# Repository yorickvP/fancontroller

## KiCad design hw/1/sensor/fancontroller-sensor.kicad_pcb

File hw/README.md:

# Hardware revisions

## Rev 1 (10-2022)
Initial prototype production series, with several issues:
* L302 has an unusable footprint, replace with Farnell 2434098 2.5uH
* 12V is 2.5V
    * R305 -> LCSC code is for 1K
    * 16K & 1K8
* Temperature sensor is placed right next to ESP32
* Would like to toggle vfan rails individually

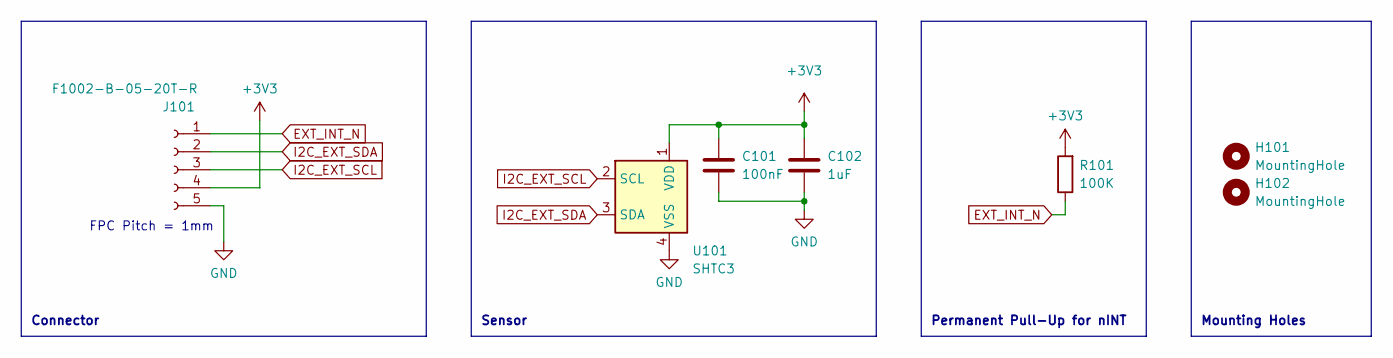
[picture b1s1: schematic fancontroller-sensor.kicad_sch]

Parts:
C101: 100nF; C_0402_1005Metric; LCSC C307331
C102: 1uF; C_0402_1005Metric; LCSC C52923
H101, H102: MountingHole; MountingHole_2.2mm_M2
J101: F1002-B-05-20T-R; LCSC C3015089
R101: 100K; R_0402_1005Metric; LCSC C25741
U101: SHTC3; Sensirion_DFN-4-1EP_2x2mm_P1mm_EP0.7x1.6mm

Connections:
+3V3: C101.1, C102.1, J101.4, R101.2, U101.1 (VDD)
EXT_INT_N: J101.1, R101.1
GND: C101.2, C102.2, J101.5, U101.4 (VSS)
I2C_EXT_SCL: J101.3, U101.2 (SCL)
I2C_EXT_SDA: J101.2, U101.3 (SDA)

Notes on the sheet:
Mounting Holes
Connector
Sensor
FPC Pitch = 1mm
Permanent Pull-Up for nINT

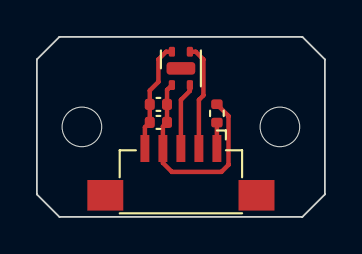
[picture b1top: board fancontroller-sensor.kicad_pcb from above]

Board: 2 copper layers, 16.0 x 10.0 mm, 7 parts (0 on the bottom side), 5 nets.

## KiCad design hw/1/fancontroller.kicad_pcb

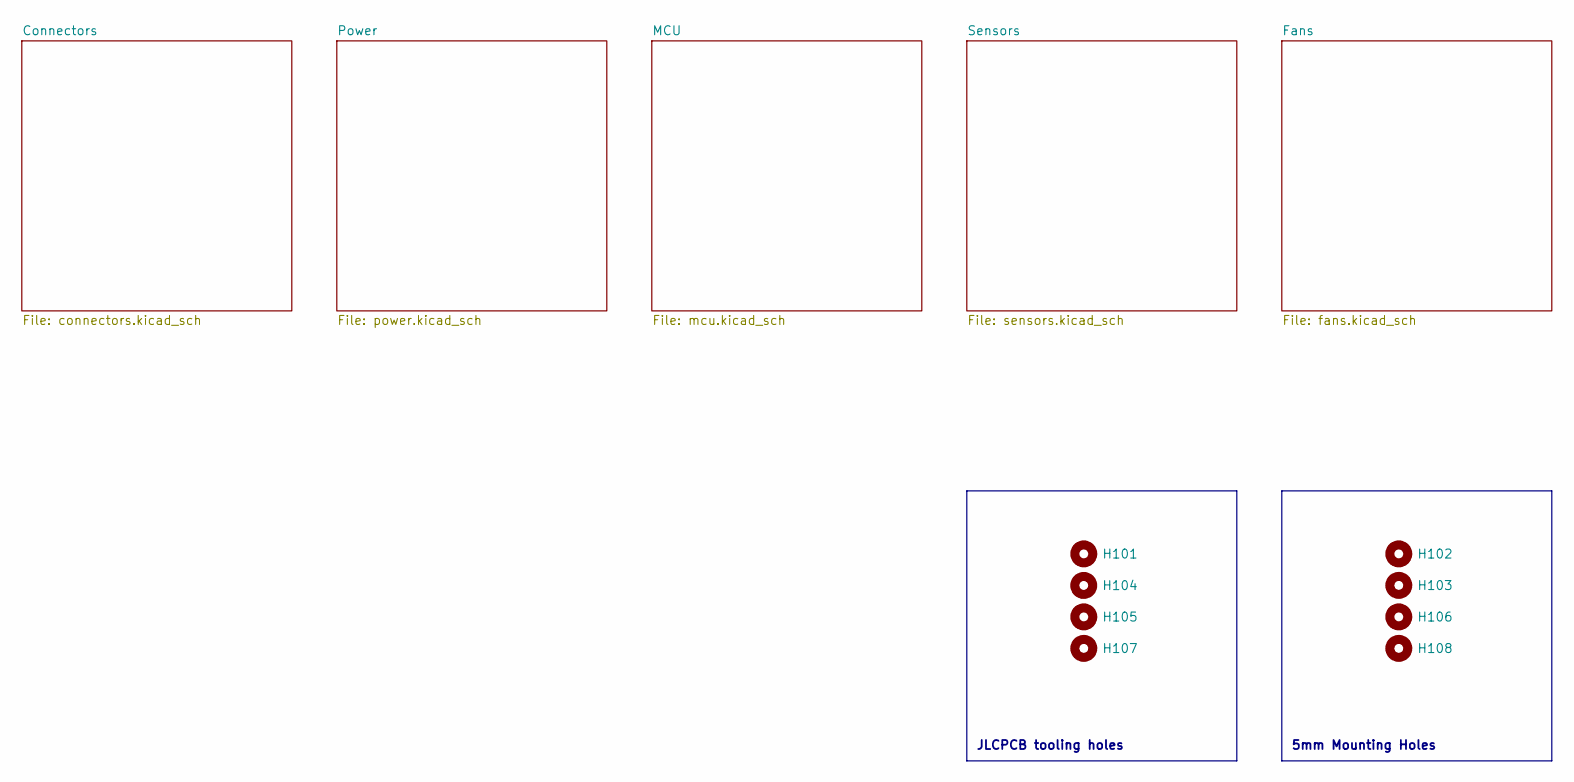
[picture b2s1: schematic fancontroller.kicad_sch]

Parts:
H101, H104, H105, H107: ToolingHole; JLCPCB tooling hole
H102, H103, H106, H108: MountingHole; MountingHole_5mm_Keepout

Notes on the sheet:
JLCPCB tooling holes
5mm Mounting Holes

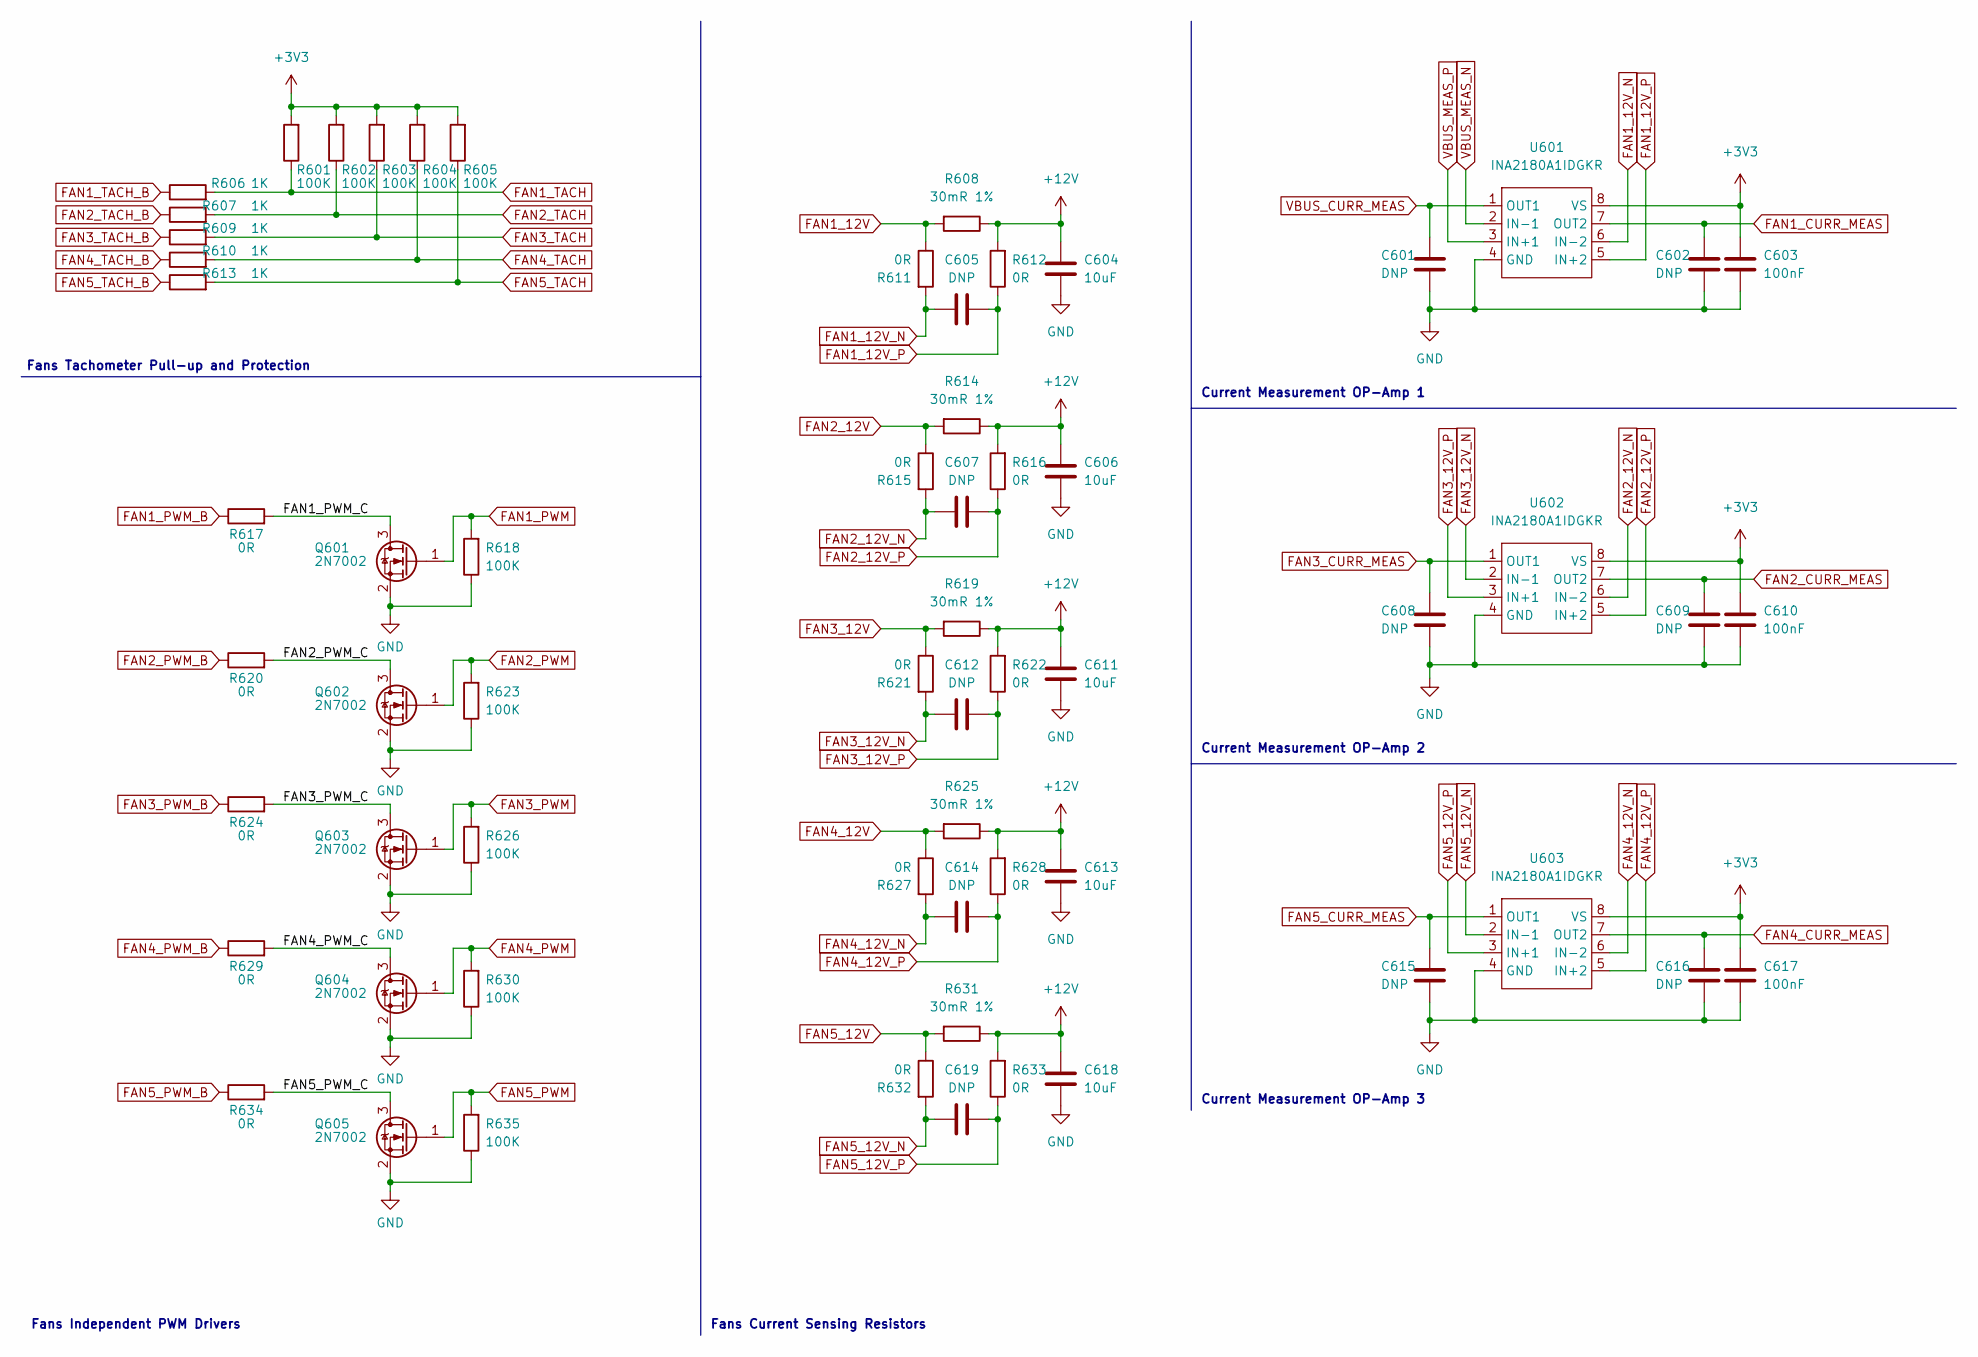
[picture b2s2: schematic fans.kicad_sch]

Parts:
C601, C602, C605, C607, C608, C609, C612, C614, C615, C616, C619: DNP; C_0402_1005Metric
C603, C610, C617: 100nF; C_0402_1005Metric; LCSC C307331
C604, C606, C611, C613, C618: 10uF; C_0805_2012Metric; LCSC C15850
Q601, Q602, Q603, Q604, Q605: 2N7002; SOT-23; LCSC C8545
R601, R602, R603, R604, R605, R618, R623, R626, R630, R635: 100K; R_0402_1005Metric; LCSC C25741
R606, R607, R609, R610, R613: 1K; R_0402_1005Metric; LCSC C11702
R608, R614, R619, R625, R631: 30mR 1%; R_0805_2012Metric; LCSC C247605
R611, R612, R615, R616, R617, R620, R621, R622, R624, R627, R628, R629, R632, R633, R634: 0R; R_0402_1005Metric; LCSC C17168
U601, U602, U603: INA2180A1IDGKR; VSSOP-8_3.0x3.0mm_P0.65mm; LCSC C2058454

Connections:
+3V3: C603.1, C610.1, C617.1, R601.2, R602.2, R603.2, R604.2, R605.2, U601.8 (VS), U602.8 (VS), U603.8 (VS); also elsewhere on the board
+12V: C604.1, C606.1, C611.1, C613.1, C618.1, R608.1, R612.2, R614.1, R616.2, R619.1, R622.2, R625.1, R628.2, R631.1, R633.2; also elsewhere on the board
/Fans/FAN1_PWM_C: Q601.3 (D), R617.2
/Fans/FAN2_PWM_C: Q602.3 (D), R620.2
/Fans/FAN3_PWM_C: Q603.3 (D), R624.2
/Fans/FAN4_PWM_C: Q604.3 (D), R629.2
/Fans/FAN5_PWM_C: Q605.3 (D), R634.2
FAN1_12V: R608.2, R611.1; also elsewhere on the board
FAN1_12V_N: C605.1, R611.2, U601.6 (IN-2)
FAN1_12V_P: C605.2, R612.1, U601.5 (IN+2)
FAN1_CURR_MEAS: C602.1, U601.7 (OUT2); also elsewhere on the board
FAN1_PWM: Q601.1 (G), R618.2; also elsewhere on the board
FAN1_PWM_B: R617.1; also elsewhere on the board
FAN1_TACH: R601.1, R606.2; also elsewhere on the board
FAN1_TACH_B: R606.1; also elsewhere on the board
FAN2_12V: R614.2, R615.1; also elsewhere on the board
FAN2_12V_N: C607.1, R615.2, U602.6 (IN-2)
FAN2_12V_P: C607.2, R616.1, U602.5 (IN+2)
FAN2_CURR_MEAS: C609.1, U602.7 (OUT2); also elsewhere on the board
FAN2_PWM: Q602.1 (G), R623.2; also elsewhere on the board
FAN2_PWM_B: R620.1; also elsewhere on the board
FAN2_TACH: R602.1, R607.2; also elsewhere on the board
FAN2_TACH_B: R607.1; also elsewhere on the board
FAN3_12V: R619.2, R621.1; also elsewhere on the board
FAN3_12V_N: C612.1, R621.2, U602.2 (IN-1)
FAN3_12V_P: C612.2, R622.1, U602.3 (IN+1)
FAN3_CURR_MEAS: C608.1, U602.1 (OUT1); also elsewhere on the board
FAN3_PWM: Q603.1 (G), R626.2; also elsewhere on the board
FAN3_PWM_B: R624.1; also elsewhere on the board
FAN3_TACH: R603.1, R609.2; also elsewhere on the board
FAN3_TACH_B: R609.1; also elsewhere on the board
FAN4_12V: R625.2, R627.1; also elsewhere on the board
FAN4_12V_N: C614.1, R627.2, U603.6 (IN-2)
FAN4_12V_P: C614.2, R628.1, U603.5 (IN+2)
FAN4_CURR_MEAS: C616.1, U603.7 (OUT2); also elsewhere on the board
FAN4_PWM: Q604.1 (G), R630.2; also elsewhere on the board
FAN4_PWM_B: R629.1; also elsewhere on the board
FAN4_TACH: R604.1, R610.2; also elsewhere on the board
FAN4_TACH_B: R610.1; also elsewhere on the board
FAN5_12V: R631.2, R632.1; also elsewhere on the board
FAN5_12V_N: C619.1, R632.2, U603.2 (IN-1)
FAN5_12V_P: C619.2, R633.1, U603.3 (IN+1)
FAN5_CURR_MEAS: C615.1, U603.1 (OUT1); also elsewhere on the board
FAN5_PWM: Q605.1 (G), R635.2; also elsewhere on the board
FAN5_PWM_B: R634.1; also elsewhere on the board
FAN5_TACH: R605.1, R613.2; also elsewhere on the board
FAN5_TACH_B: R613.1; also elsewhere on the board
VBUS_CURR_MEAS: C601.1, U601.1 (OUT1); also elsewhere on the board
VBUS_MEAS_N: U601.2 (IN-1); also elsewhere on the board
VBUS_MEAS_P: U601.3 (IN+1); also elsewhere on the board

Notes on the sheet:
Current Measurement OP-Amp 3
Fans Independent PWM Drivers
Current Measurement OP-Amp 1
Fans Current Sensing Resistors
Fans Tachometer Pull-up and Protection
Current Measurement OP-Amp 2

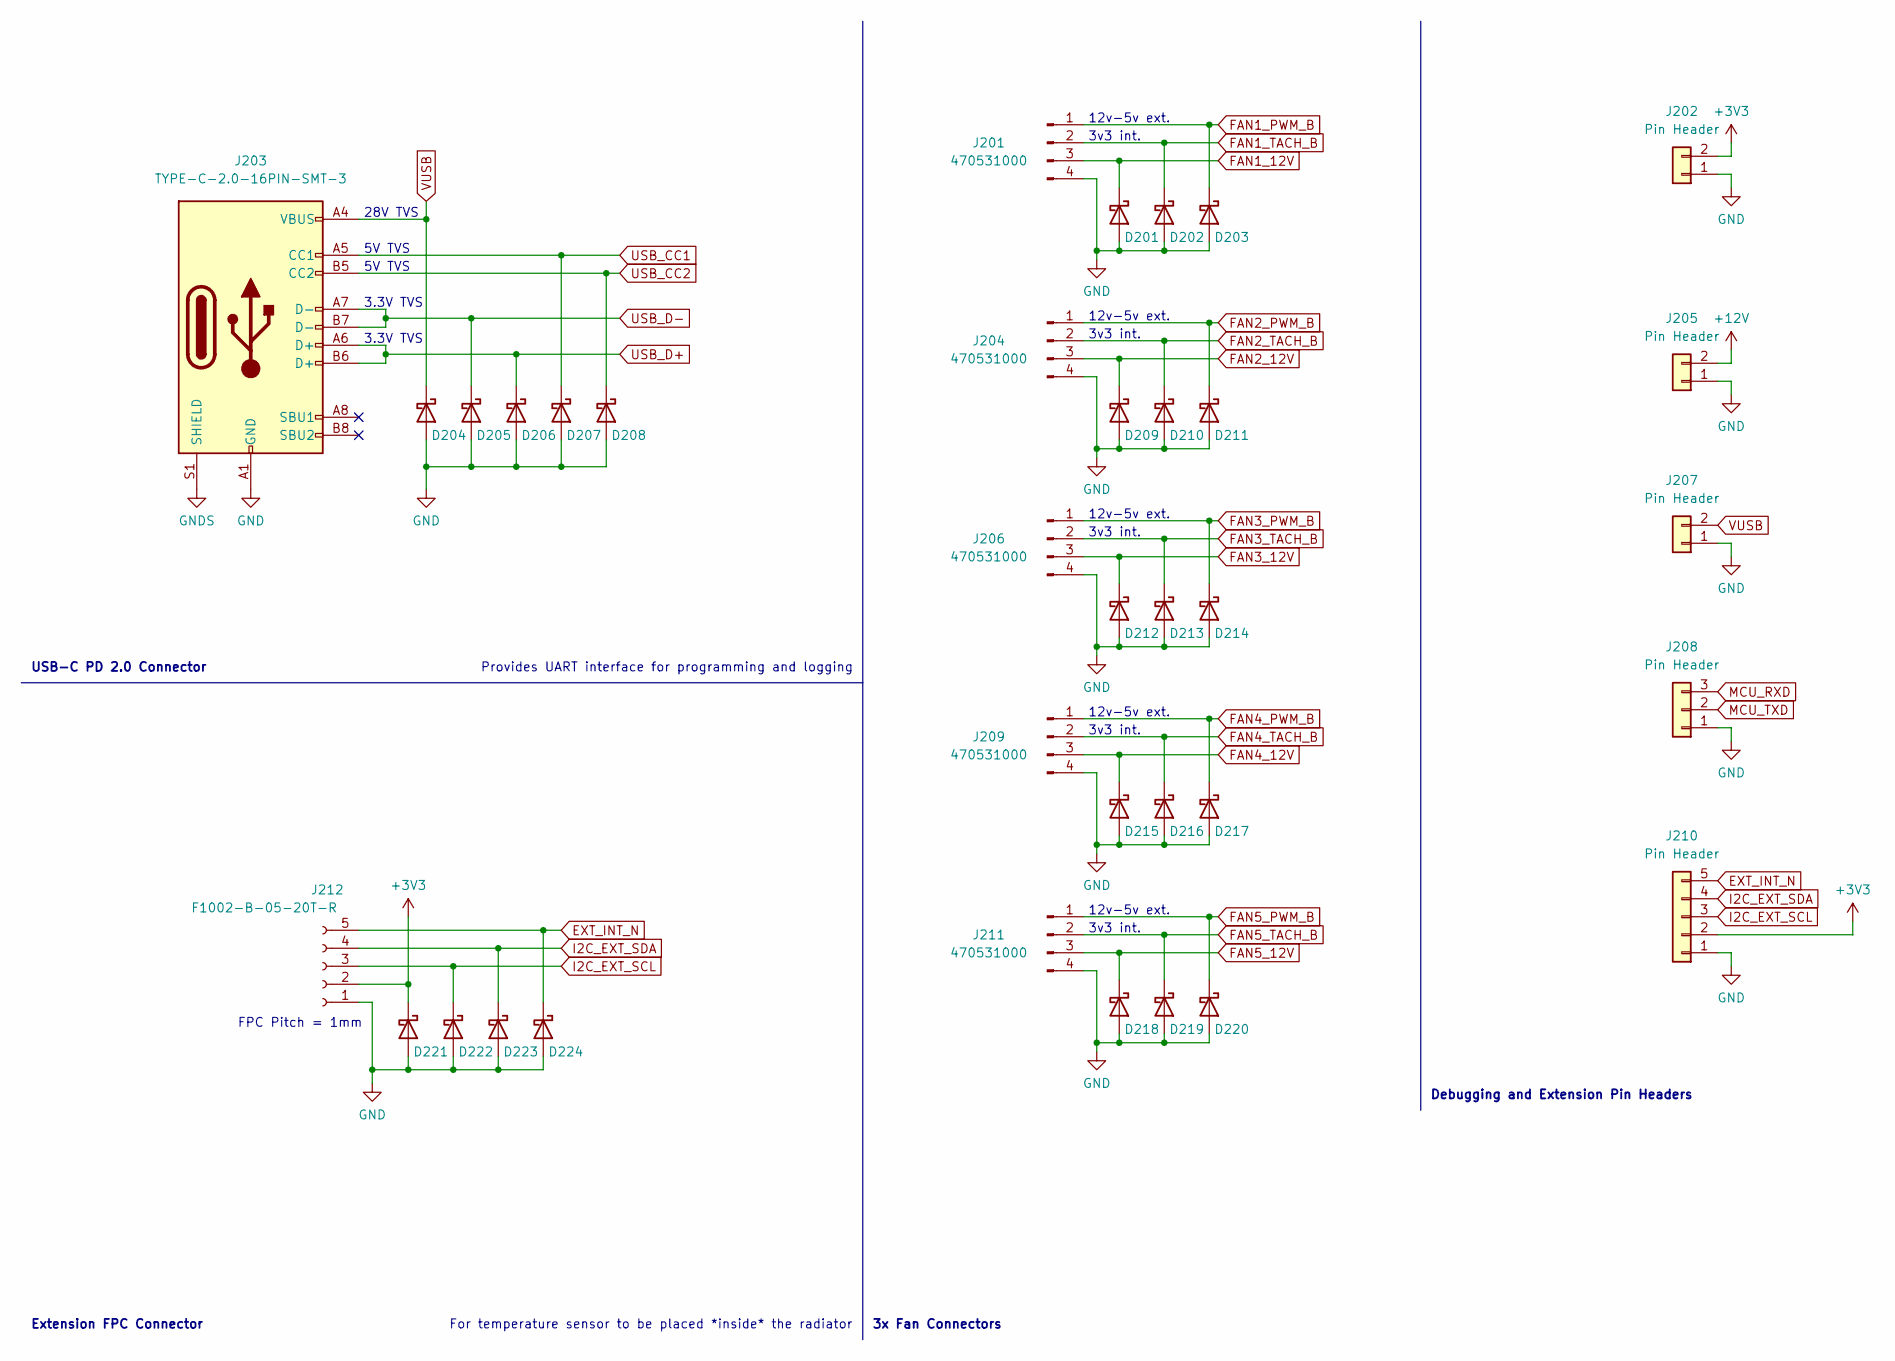
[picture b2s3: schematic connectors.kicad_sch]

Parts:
D201, D203, D209, D211, D212, D214, D215, D217, D218, D220: AQ4022-01FTG; D_SOD-323; LCSC C468894
D202, D205, D206, D210, D213, D216, D219, D221, D222, D223, D224: ESD9L3.3ST5G; D_SOD-923; LCSC C233387
D204: SJD12A28L01; D_SOD-123S; LCSC C313190
D207, D208: ESD9X5.0ST5G; D_SOD-923; LCSC C87910
J201, J204, J206, J209, J211: 470531000; Molex_470531000_PWM_fan; LCSC C240840
J202, J205, J207: Pin Header; PinHeader_1x02_P2.54mm_Vertical
J203: TYPE-C-2.0-16PIN-SMT-3; LCSC C2987386
J208: Pin Header; PinHeader_1x03_P2.54mm_Vertical
J210: Pin Header; PinHeader_1x05_P2.54mm_Vertical
J212: F1002-B-05-20T-R; LCSC C3015089

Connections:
+3V3: D221.1 (K), J202.2, J210.2, J212.2; also elsewhere on the board
+12V: J205.2; also elsewhere on the board
EXT_INT_N: D224.1 (K), J210.5, J212.5; also elsewhere on the board
FAN1_12V: D201.1 (K), J201.3; also elsewhere on the board
FAN1_PWM_B: D203.1 (K), J201.1; also elsewhere on the board
FAN1_TACH_B: D202.1 (K), J201.2; also elsewhere on the board
FAN2_12V: D209.1 (K), J204.3; also elsewhere on the board
FAN2_PWM_B: D211.1 (K), J204.1; also elsewhere on the board
FAN2_TACH_B: D210.1 (K), J204.2; also elsewhere on the board
FAN3_12V: D212.1 (K), J206.3; also elsewhere on the board
FAN3_PWM_B: D214.1 (K), J206.1; also elsewhere on the board
FAN3_TACH_B: D213.1 (K), J206.2; also elsewhere on the board
FAN4_12V: D215.1 (K), J209.3; also elsewhere on the board
FAN4_PWM_B: D217.1 (K), J209.1; also elsewhere on the board
FAN4_TACH_B: D216.1 (K), J209.2; also elsewhere on the board
FAN5_12V: D218.1 (K), J211.3; also elsewhere on the board
FAN5_PWM_B: D220.1 (K), J211.1; also elsewhere on the board
FAN5_TACH_B: D219.1 (K), J211.2; also elsewhere on the board
GNDS: J203.S1 (SHIELD)
I2C_EXT_SCL: D222.1 (K), J210.3, J212.3; also elsewhere on the board
I2C_EXT_SDA: D223.1 (K), J210.4, J212.4; also elsewhere on the board
MCU_RXD: J208.3; also elsewhere on the board
MCU_TXD: J208.2; also elsewhere on the board
USB_CC1: D207.1 (K), J203.A5 (CC1); also elsewhere on the board
USB_CC2: D208.1 (K), J203.B5 (CC2); also elsewhere on the board
USB_D+: D206.1 (K), J203.A6 (D+), J203.B6 (D+); also elsewhere on the board
USB_D-: D205.1 (K), J203.A7 (D-), J203.B7 (D-); also elsewhere on the board
VUSB: D204.1 (K), J203.A4 (VBUS), J203.A9 (VBUS), J203.B4 (VBUS), J203.B9 (VBUS), J207.2; also elsewhere on the board

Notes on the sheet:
Debugging and Extension Pin Headers
12v-5v ext.
5V TVS
3.3V TVS
FPC Pitch = 1mm
Provides UART interface for programming and logging
28V TVS
For temperature sensor to be placed *inside* the radiator
3x Fan Connectors
3v3 int.
USB-C PD 2.0 Connector
Extension FPC Connector

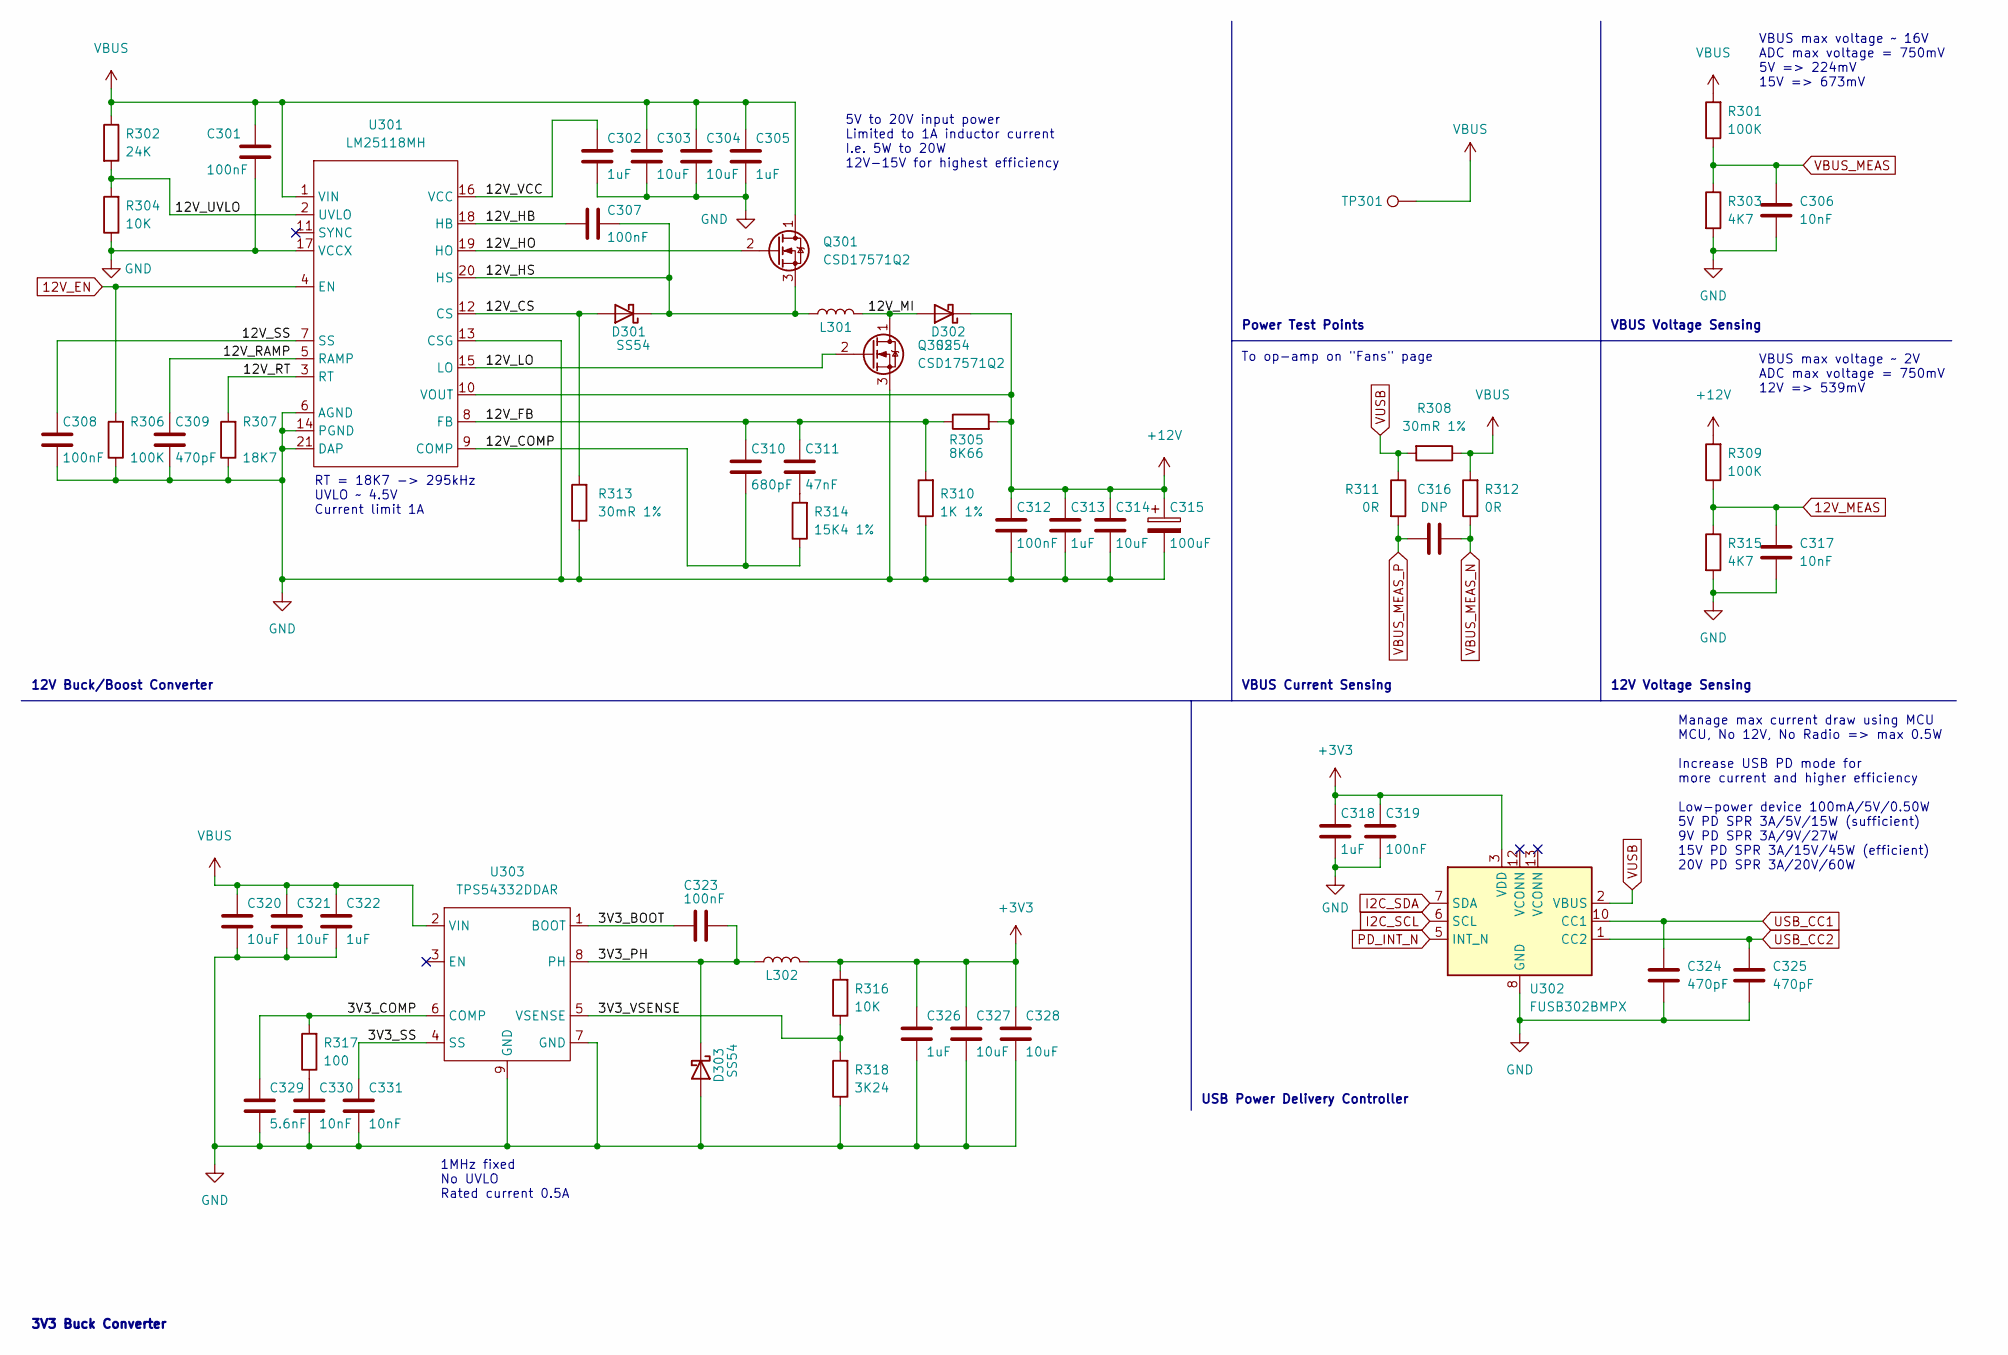
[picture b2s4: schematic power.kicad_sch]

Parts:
C301, C307, C308, C312, C319, C323: 100nF; C_0402_1005Metric; LCSC C307331
C302, C305, C313, C318, C322, C326: 1uF; C_0402_1005Metric; LCSC C52923
C303, C304, C314, C320, C321, C327, C328: 10uF; C_0805_2012Metric; LCSC C15850
C306, C317, C330, C331: 10nF; C_0402_1005Metric; LCSC C15195
C309, C324, C325: 470pF; C_0402_1005Metric; LCSC C1537
C310: 680pF; C_0402_1005Metric; LCSC C338094
C311: 47nF; C_0402_1005Metric; LCSC C368599
C315: 100uF; CP_Elec_6.3x7.7; LCSC C3339
C316: DNP; C_0402_1005Metric
C329: 5.6nF; C_0402_1005Metric; LCSC C115688
D301, D302, D303: SS54; D_SMA; LCSC C22452
L301: CDRH127NP-180MC; L_12x12mm_H8mm; LCSC C2454078
L302: SCDS6D38T-220M-S-N; L_7.3x7.3_H4.5; LCSC C329694
Q301, Q302: CSD17571Q2; LCSC C962382
R301, R306, R309: 100K; R_0402_1005Metric; LCSC C25741
R302: 24K; R_0402_1005Metric; LCSC C25769
R303, R315: 4K7; R_0402_1005Metric; LCSC C25900
R304, R316: 10K; R_0402_1005Metric; LCSC C25744
R305: 8K66; R_0402_1005Metric; LCSC C11702
R307: 18K7; R_0402_1005Metric; LCSC C11476
R308, R313: 30mR 1%; R_0805_2012Metric; LCSC C247605
R310: 1K 1%; R_0402_1005Metric; LCSC C11702
R311, R312: 0R; R_0402_1005Metric; LCSC C17168
R314: 15K4 1%; R_0402_1005Metric; LCSC C62740
R317: 100; R_0402_1005Metric; LCSC C25076
R318: 3K24; R_0402_1005Metric; LCSC C162875
TP301: TestPoint; TestPoint_THTPad_D1.0mm_Drill0.5mm
U301: LM25118MH; HTSSOP-20-1EP_4.4x6.5mm_P0.65mm_EP2.74x3.86mm; LCSC C470962
U302: FUSB302BMPX; WQFN-14-1EP_2.5x2.5mm_P0.5mm_EP1.45x1.45mm
U303: TPS54332DDAR; SOIC-8-1EP_3.9x4.9mm_P1.27mm_EP2.29x3mm_ThermalVias; LCSC C41312

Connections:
12V_EN: R306.2, U301.4 (EN); also elsewhere on the board
12V_MEAS: C317.1, R309.1, R315.1; also elsewhere on the board
+3V3: C318.1, C319.1, C326.1, C327.1, C328.1, L302.2, R316.2, U302.3 (VDD), U302.4 (VDD); also elsewhere on the board
+12V: C312.1, C313.1, C314.1, C315.1, D302.1 (K), R305.2, R309.2, U301.10 (VOUT); also elsewhere on the board
/Power/3V3_BOOT: C323.2, U303.1 (BOOT)
/Power/3V3_COMP: C329.1, R317.2, U303.6 (COMP)
/Power/3V3_PH: C323.1, D303.1 (K), L302.1, U303.8 (PH)
/Power/3V3_SS: C331.1, U303.4 (SS)
/Power/3V3_VSENSE: R316.1, R318.2, U303.5 (VSENSE)
/Power/12V_COMP: C310.2, R314.1, U301.9 (COMP)
/Power/12V_CS: D301.2 (A), R313.2, U301.12 (CS)
/Power/12V_FB: C310.1, C311.1, R305.1, R310.2, U301.8 (FB)
/Power/12V_HB: C307.2, U301.18 (HB)
/Power/12V_HO: Q301.2 (G), U301.19 (HO)
/Power/12V_HS: C307.1, D301.1 (K), L301.1, Q301.3 (S), U301.20 (HS)
/Power/12V_LO: Q302.2 (G), U301.15 (LO)
/Power/12V_MI: D302.2 (A), L301.2, Q302.1 (D)
/Power/12V_RAMP: C309.1, U301.5 (RAMP)
/Power/12V_RT: R307.2, U301.3 (RT)
/Power/12V_SS: C308.1, U301.7 (SS)
/Power/12V_UVLO: R302.2, R304.2, U301.2 (UVLO)
/Power/12V_VCC: C302.1, U301.16 (VCC)
I2C_SCL: U302.6 (SCL); also elsewhere on the board
I2C_SDA: U302.7 (SDA); also elsewhere on the board
unnamed: C311.2, R314.2
unnamed: C330.1, R317.1
PD_INT_N: U302.5 (INT_N); also elsewhere on the board
USB_CC1: C324.1, U302.10 (CC1), U302.11 (CC1); also elsewhere on the board
USB_CC2: C325.1, U302.1 (CC2), U302.14 (CC2); also elsewhere on the board
VBUS: C301.1, C303.1, C304.1, C305.1, C320.1, C321.1, C322.1, Q301.1 (D), R301.2, R302.1, R308.1, R312.2, TP301.1, U301.1 (VIN), U303.2 (VIN)
VBUS_MEAS: C306.1, R301.1, R303.1; also elsewhere on the board
VBUS_MEAS_N: C316.2, R312.1; also elsewhere on the board
VBUS_MEAS_P: C316.1, R311.2; also elsewhere on the board
VUSB: R308.2, R311.1, U302.2 (VBUS); also elsewhere on the board

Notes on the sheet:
VBUS Voltage Sensing
RT = 18K7 -> 295kHz UVLO ~ 4.5V Current limit 1A
1MHz fixed No UVLO Rated current 0.5A
3V3 Buck Converter
VBUS max voltage ~ 16V ADC max voltage = 750mV 5V => 224mV 15V => 673mV
12V Buck/Boost Converter
USB Power Delivery Controller
VBUS Current Sensing
To op-amp on "Fans" page
5V to 20V input power Limited to 1A inductor current I.e. 5W to 20W 12V-15V for highest efficiency
12V Voltage Sensing
VBUS max voltage ~ 2V ADC max voltage = 750mV 12V => 539mV
Manage max current draw using MCU MCU, No 12V, No Radio => max 0.5W Increase USB PD mode for more current and higher efficiency Low-power device 100mA/5V/0.50W 5V PD SPR 3A/5V/15W (sufficient) 9V PD SPR 3A/9V/27W 15V PD SPR 3A/15V/45W (efficient) 20V PD SPR 3A/20V/60W
Power Test Points

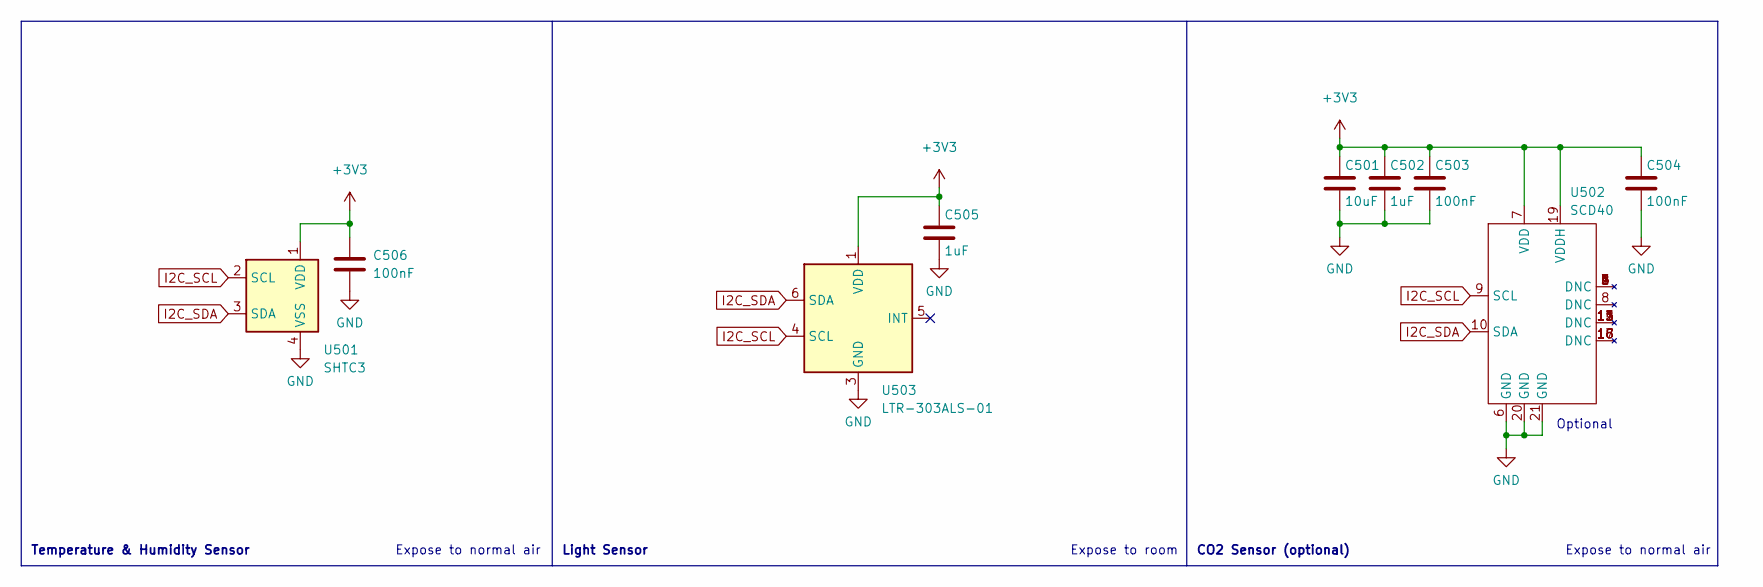
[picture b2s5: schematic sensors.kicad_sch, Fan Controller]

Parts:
C501: 10uF; C_0402_1005Metric; LCSC C15525
C502, C505: 1uF; C_0402_1005Metric; LCSC C52923
C503, C504, C506: 100nF; C_0402_1005Metric; LCSC C307331
U501: SHTC3; Sensirion_DFN-4-1EP_2x2mm_P1mm_EP0.7x1.6mm; LCSC C194656
U502: SCD40; SCD4x
U503: LTR-303ALS-01; Lite-On_LTR-303ALS-01; LCSC C364577

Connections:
+3V3: C501.1, C502.1, C503.1, C504.1, C505.1, C506.1, U501.1 (VDD), U502.7 (VDD), U502.19 (VDDH), U503.1 (VDD); also elsewhere on the board
I2C_SCL: U501.2 (SCL), U502.9 (SCL), U503.4 (SCL); also elsewhere on the board
I2C_SDA: U501.3 (SDA), U502.10 (SDA), U503.6 (SDA); also elsewhere on the board

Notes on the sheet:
Expose to room
Optional
Expose to normal air
Light Sensor
CO2 Sensor (optional)
Temperature & Humidity Sensor

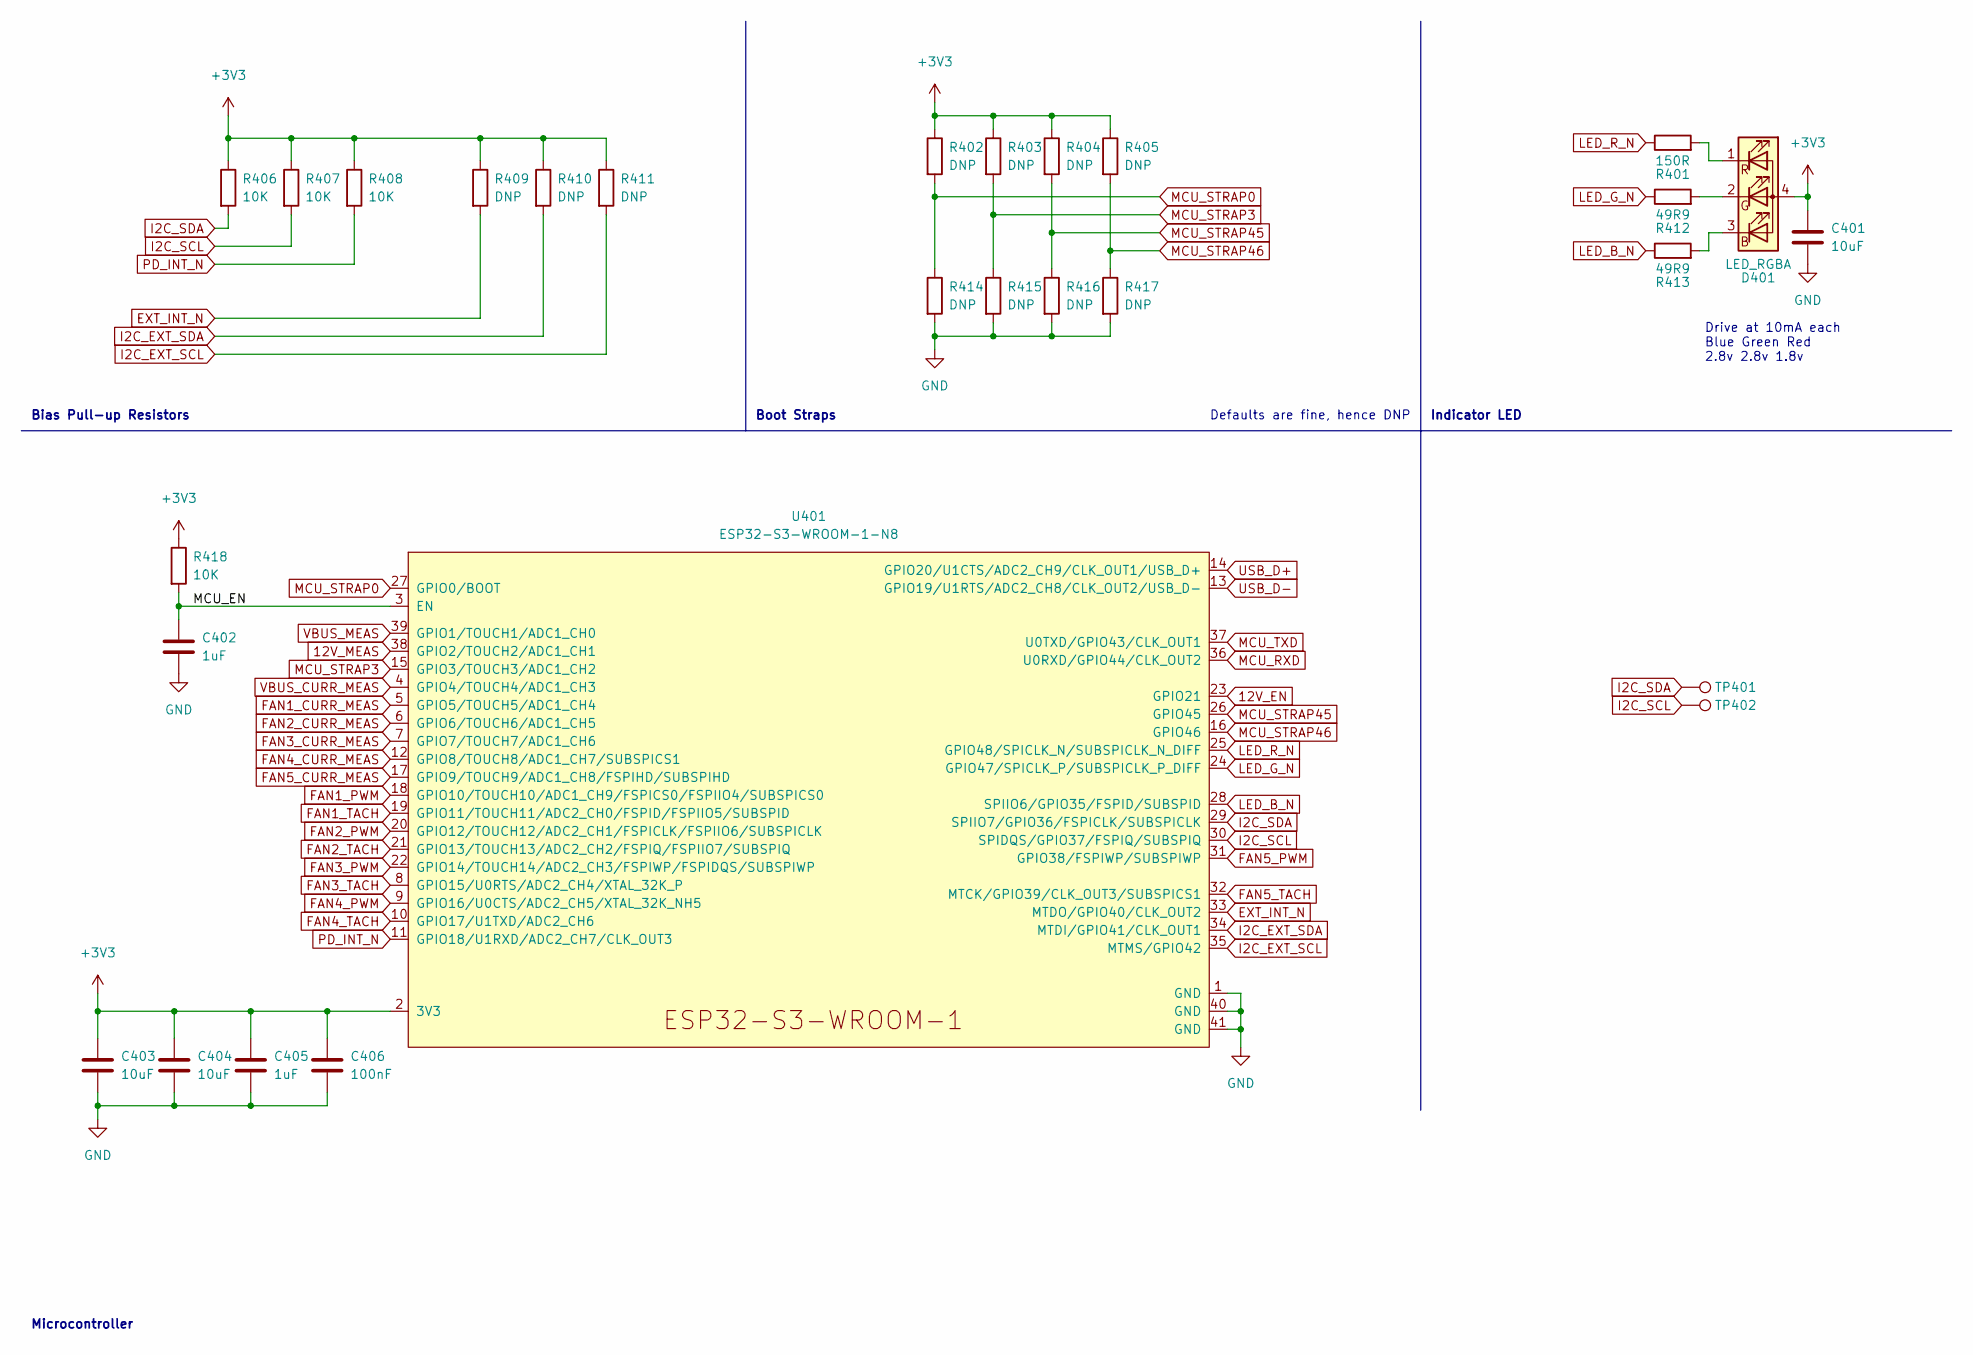
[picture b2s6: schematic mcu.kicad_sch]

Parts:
C401, C403, C404: 10uF; C_0402_1005Metric; LCSC C15525
C402, C405: 1uF; C_0402_1005Metric; LCSC C52923
C406: 100nF; C_0402_1005Metric; LCSC C307331
D401: LED_RGBA; LED_LiteOn_LTST-C19HE1WT; LCSC C427425
R401: 150R; R_0402_1005Metric; LCSC C25082
R402, R403, R404, R405, R409, R410, R411, R414, R415, R416, R417: DNP; R_0402_1005Metric
R406, R407, R408, R418: 10K; R_0402_1005Metric; LCSC C25744
R412, R413: 49R9; R_0402_1005Metric; LCSC C25120
TP401, TP402: TestPoint; TestPoint_THTPad_D1.0mm_Drill0.5mm
U401: ESP32-S3-WROOM-1-N8; ESP32-S3-WROOM-1; LCSC C2913198

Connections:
12V_EN: U401.23 (GPIO21); also elsewhere on the board
12V_MEAS: U401.38 (GPIO2/TOUCH2/ADC1_CH1); also elsewhere on the board
+3V3: C401.1, C403.1, C404.1, C405.1, C406.1, D401.4 (A), R402.1, R403.1, R404.1, R405.1, R406.1, R407.1, R408.1, R409.1, R410.1, R411.1, R418.1, U401.2 (3V3); also elsewhere on the board
/MCU/MCU_EN: C402.1, R418.2, U401.3 (EN)
EXT_INT_N: R409.2, U401.33 (MTDO/GPIO40/CLK_OUT2); also elsewhere on the board
FAN1_CURR_MEAS: U401.5 (GPIO5/TOUCH5/ADC1_CH4); also elsewhere on the board
FAN1_PWM: U401.18 (GPIO10/TOUCH10/ADC1_CH9/FSPICS0/FSPIIO4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); also elsewhere on the board
FAN1_TACH: U401.19 (GPIO11/TOUCH11/ADC2_CH0/FSPID/FSPIIO5/S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); also elsewhere on the board
FAN2_CURR_MEAS: U401.6 (GPIO6/TOUCH6/ADC1_CH5); also elsewhere on the board
FAN2_PWM: U401.20 (GPIO12/TOUCH12/ADC2_CH1/FSPICLK/FSPIIO6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); also elsewhere on the board
FAN2_TACH: U401.21 (GPIO13/TOUCH13/ADC2_CH2/FSPIQ/FSPIIO7/S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); also elsewhere on the board
FAN3_CURR_MEAS: U401.7 (GPIO7/TOUCH7/ADC1_CH6); also elsewhere on the board
FAN3_PWM: U401.22 (GPIO14/TOUCH14/ADC2_CH3/FSPIWP/FSPIDQS/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); also elsewhere on the board
FAN3_TACH: U401.8 (GPIO15/U0RTS/ADC2_CH4/XTAL_32K_P); also elsewhere on the board
FAN4_CURR_MEAS: U401.12 (GPIO8/TOUCH8/ADC1_CH7/SUBSPICS1); also elsewhere on the board
FAN4_PWM: U401.9 (GPIO16/U0CTS/ADC2_CH5/XTAL_32K_NH5); also elsewhere on the board
FAN4_TACH: U401.10 (GPIO17/U1TXD/ADC2_CH6); also elsewhere on the board
FAN5_CURR_MEAS: U401.17 (GPIO9/TOUCH9/ADC1_CH8/FSPIHD/SUBSPIHD); also elsewhere on the board
FAN5_PWM: U401.31 (GPIO38/FSPIWP/SUBSPIWP); also elsewhere on the board
FAN5_TACH: U401.32 (MTCK/GPIO39/CLK_OUT3/SUBSPICS1); also elsewhere on the board
I2C_EXT_SCL: R411.2, U401.35 (MTMS/GPIO42); also elsewhere on the board
I2C_EXT_SDA: R410.2, U401.34 (MTDI/GPIO41/CLK_OUT1); also elsewhere on the board
I2C_SCL: R407.2, TP402.1, U401.30 (SPIDQS/GPIO37/FSPIQ/SUBSPIQ); also elsewhere on the board
I2C_SDA: R406.2, TP401.1, U401.29 (SPIIO7/GPIO36/FSPICLK/SUBSPICLK); also elsewhere on the board
LED_B_N: R413.1, U401.28 (SPIIO6/GPIO35/FSPID/SUBSPID)
LED_G_N: R412.1, U401.24 (GPIO47/SPICLK_P/SUBSPICLK_P_DIFF)
LED_R_N: R401.1, U401.25 (GPIO48/SPICLK_N/SUBSPICLK_N_DIFF)
MCU_RXD: U401.36 (U0RXD/GPIO44/CLK_OUT2); also elsewhere on the board
MCU_STRAP0: R402.2, R414.1, U401.27 (GPIO0/BOOT)
MCU_STRAP3: R403.2, R415.1, U401.15 (GPIO3/TOUCH3/ADC1_CH2)
MCU_STRAP45: R404.2, R416.1, U401.26 (GPIO45)
MCU_STRAP46: R405.2, R417.1, U401.16 (GPIO46)
MCU_TXD: U401.37 (U0TXD/GPIO43/CLK_OUT1); also elsewhere on the board
unnamed: D401.1 (RK), R401.2
unnamed: D401.2 (GK), R412.2
unnamed: D401.3 (BK), R413.2
PD_INT_N: R408.2, U401.11 (GPIO18/U1RXD/ADC2_CH7/CLK_OUT3); also elsewhere on the board
USB_D+: U401.14 (GPIO20/U1CTS/ADC2_CH9/CLK_OUT1/USB_D+); also elsewhere on the board
USB_D-: U401.13 (GPIO19/U1RTS/ADC2_CH8/CLK_OUT2/USB_D-); also elsewhere on the board
VBUS_CURR_MEAS: U401.4 (GPIO4/TOUCH4/ADC1_CH3); also elsewhere on the board
VBUS_MEAS: U401.39 (GPIO1/TOUCH1/ADC1_CH0); also elsewhere on the board

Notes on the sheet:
Defaults are fine, hence DNP
Drive at 10mA each Blue Green Red 2.8v 2.8v 1.8v
Boot Straps
Indicator LED
Bias Pull-up Resistors
Microcontroller

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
